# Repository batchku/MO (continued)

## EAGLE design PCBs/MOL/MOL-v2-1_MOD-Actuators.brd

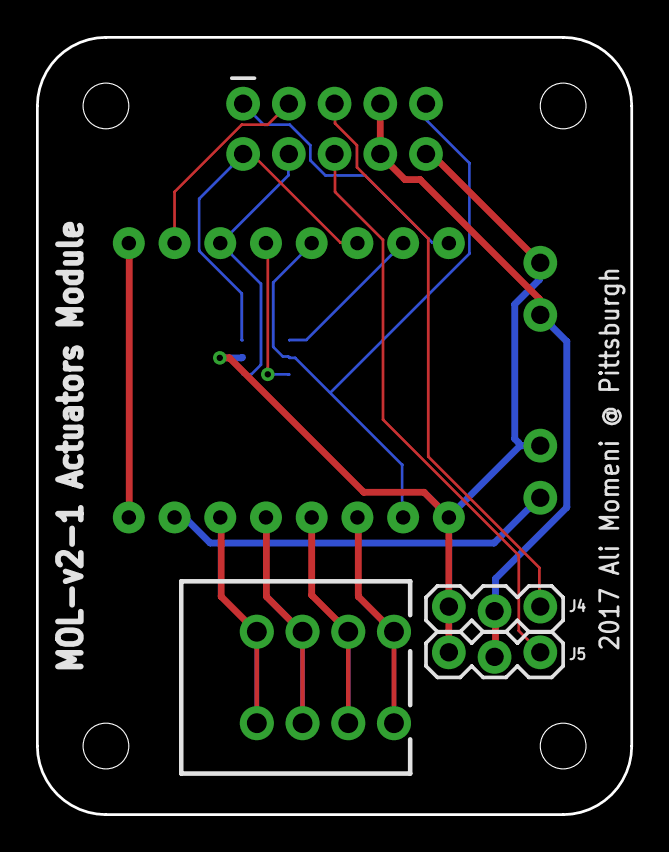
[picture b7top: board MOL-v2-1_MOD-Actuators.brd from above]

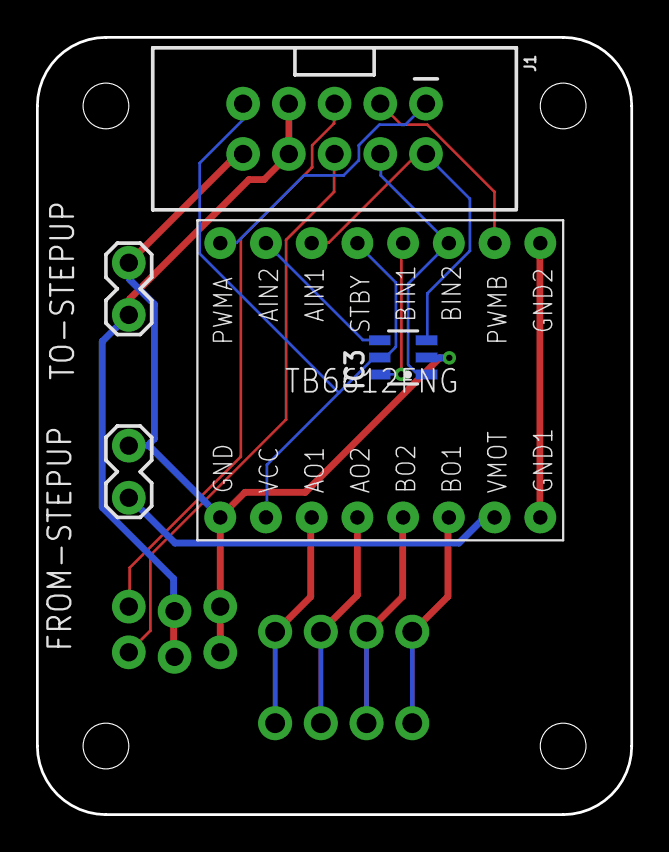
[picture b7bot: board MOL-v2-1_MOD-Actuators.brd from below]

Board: 2 copper layers, 33.0 x 43.2 mm, 8 parts (5 on the bottom side), 17 nets.

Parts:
FROM-STEPUP: 1X02_LOCK
IC3: SN74LVC2G04DBV; SOT23-6
J1: ACTUATORS; 2X5-SHROUDED_LOCK
J4: SERVO 1; 1X03_LOCK@1
J5: SERVO 2; 1X03_LOCK@1
MOTORS1: SPRINGTERMINAL-2.54MM-4
TO-STEPUP: 1X02_LOCK
U$7: POLOLU_TB6612FNG

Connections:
+3V3: IC3.5, J1.9, U$7.STBY, U$7.VCC
+5V: J1.7, J1.8, J4.2, J5.2, TO-STEPUP.1
GND: FROM-STEPUP.1, IC3.2, J1.10, J4.1, J5.1, TO-STEPUP.2, U$7.GND
GND_MOT: U$7.GND1, U$7.GND2
M_AIN: IC3.3, J1.2, U$7.AIN1
M_BIN: IC3.1, J1.4, U$7.BIN2
M_PWMA: J1.1, U$7.PWMA
M_PWMB: J1.3, U$7.PWMB
unnamed: MOTORS1.P$1, U$7.AO1
unnamed: MOTORS1.P$2, U$7.AO2
unnamed: MOTORS1.P$3, U$7.BO2
unnamed: MOTORS1.P$4, U$7.BO1
unnamed: IC3.6, U$7.BIN1
unnamed: IC3.4, U$7.AIN2
S1: J1.5, J4.3
S2: J1.6, J5.3
VMOT: FROM-STEPUP.2, U$7.VMOT
